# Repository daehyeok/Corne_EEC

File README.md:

# Corne EEC (Corne Extended Electrostatic Capacitive)

A Corne-based electrostatic capacitive (EC) keyboard featuring a number row and one additional thumb key.

> [!WARNING]
> I am not an electrical engineer. PCB design may not be optimized and could contain bugs. Use this project at your own risk.

## Features
* Corne-like design with a number row and 4 thumb keys, totaling 28 keys per half.
* Onboard STM32G431KBT6 MCU and USB-C with ESD protection.
* No through-hole components.
* ~~Extra PCB connectivity via a 1x06 FFC connector~~ **Rev2's FFC connector located upside down.**

## Firmware

The Rust-based firmware is hosted in a separate repository: [daehyeok/corne-eec-rs](https://github.com/daehyeok/corne-eec-rs).

## Credit

# Credit & Reference.

* [tomsmalley/custom-topre-guide](https://github.com/tomsmalley/custom-topre-guide): An invaluable resource for understanding custom Topre-style keyboards.
* [Cipulot](https://github.com/Cipulot)'s multiple PCB and firmware projects: A great source of inspiration for keyboard hardware and firmware development.
*  This project is forked from [Cipulot/CorneECRevival](https://github.com/Cipulot/CorneECRevival).

## Copyright

This project is released under the MIT License. Refer to the `LICENCE.md` file for details.

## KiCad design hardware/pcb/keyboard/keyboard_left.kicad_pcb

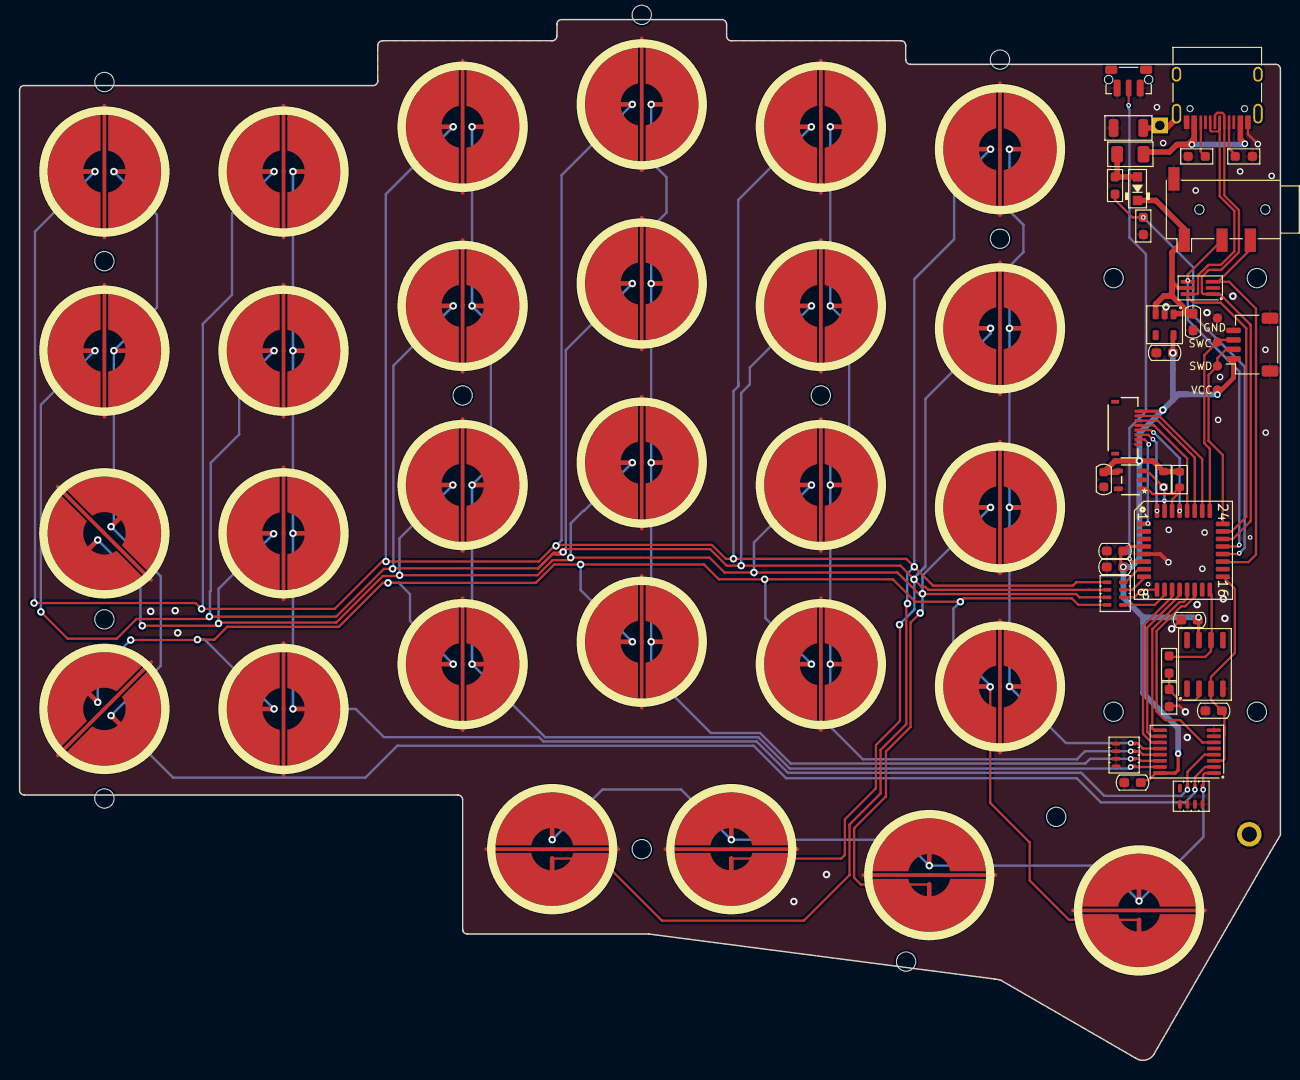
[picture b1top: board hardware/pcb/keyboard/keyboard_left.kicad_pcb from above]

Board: 2 copper layers, 133.8 x 110.4 mm, 108 parts (1 on the bottom side), 46 nets.

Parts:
C2, C3, C4: 0.1uF; C_0603_1608Metric_Pad1.05x0.95mm
C5: 4.7u; C_0603_1608Metric_Pad1.05x0.95mm
C8, C9: 1uF; C_0603_1608Metric_Pad1.05x0.95mm
C10: 220pF; C_0603_1608Metric_Pad1.05x0.95mm
C14: 10n; C_0603_1608Metric
D1: 1N5819; D_SOD-323_HandSoldering
F1: 500mA; Fuse_1206_3216Metric
G1, G2, G3, G4, G5, G6, G7, G8, G9, G10, G11, G12, G13, G14, G15, G16, G17, G18, G19, G20, G21, G23, G24, G25, G26, G27, G28: ecs_housing_graphic
G22: ecs_housing_graphic_1.5U
H0: SMT-SO-M1.6-with-ring
H1, H2, H3, H4, H5, H6, H7, H8, H9, H10, H11, H12, H13, H14, H15, H16: MountingHole_2.05mm
H17: PinHeader_1x01
J1: SM04B-SRSS-TB; JST_SH_SM04B-SRSS-TB_1x04-1MP_P1.00mm_Horizontal
J2: PJ320D; Jack_3.5mm_PJ320D_Horizontal
J3: HRO_TYPE-C-31-M-12; USB_C_Receptacle_HRO_TYPE-C-31-M-12
J4: Conn_01x08_MountingPin; CONN8_FH34SRJ_HIR
L1: 60R@100MHz; L_1206_3216Metric
R2, R3: 5.1k; R_0603_1608Metric_Pad0.98x0.95mm
R4: < 800; R_0603_1608Metric_Pad0.98x0.95mm
R5, R6: 1k; R_0603_1608Metric_Pad0.98x0.95mm
R7: 100k; R_0603_1608Metric_Pad0.98x0.95mm
R9, R10: 10k; R_0603_1608Metric
RN1, RN2: 1k R_Array_Concave_4x0603; R_Array_Concave_4x0603
RN3: 100 R_Array_Convex_4x1206; R_Array_Concave_4x0603
SW1, SW2, SW3, SW4, SW5, SW6, SW7, SW8, SW9, SW10, SW11, SW12, SW13, SW14, SW15, SW16, SW17, SW18, SW19, SW20, SW21, SW22, SW23, SW24, SW25, SW26, SW27, SW28: ecs_pad_no_ring
SW29: PTS845; SW_Push_1P1T-MP_NO_Horizontal_Alps_SKRTLAE010
TP1: PinHeader_1x04_P2.54mm_test_pad
U1: 74HC4051; TSSOP-16_4.4x5mm_P0.65mm
U2: OPA350UA; SO-8_3.9x4.9mm_P1.27mm
U3: DT1446-04S; SOT-363_SC-70-6_Handsoldering
U4: XC6220B331MR-G; SOT-23-5
U5: STM32G0B1KETx; LQFP-32_7x7mm_P0.8mm
U6: 24FC01T-I/OT; SOT-23-5_2P9X1P6_MCH

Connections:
+3V3: C2.2, C3.2, C4.1, C5.1, C8.1, C14.2, J1.1, J4.1, R9.2, R10.1, TP1.1, U1.16 (VCC), U2.7 (V+), U4.5 (VOUT), U5.4 (VDD), U6.4 (VCC)
+5V: C9.1, D1.1 (K), J2.T, U3.5 (VP), U4.1 (VIN), U4.3 (EN)
/NRST: SW29.2, U5.6 (PF2)
/PA15: J4.2, U5.26 (PA15)
/PB3: J4.3, U5.27 (PB3)
/PB4: J4.4, U5.28 (PB4)
/PB5: J4.5, U5.29 (PB5)
/PB8: J4.6, U5.32 (PB8)
/PB9: J4.7, U5.1 (PB9)
A1: RN1.2 (R2.1), SW11.1, SW12.1, SW13.1, SW25.1, U1.14 (A1)
A2: RN1.1 (R1.1), SW8.1, SW9.1, SW10.1, SW24.1, U1.15 (A2)
A3: RN1.4 (R4.1), SW17.1, SW18.1, SW19.1, SW27.1, U1.12 (A3)
A4: RN2.1 (R1.1), SW20.1, SW21.1, SW22.1, SW28.1, U1.1 (A4)
A6: RN2.2 (R2.1), SW1.1, SW2.1, SW3.1, SW4.1, U1.2 (A6)
A7: RN2.3 (R3.1), SW5.1, SW6.1, SW7.1, SW23.1, U1.4 (A7)
ADC: R7.1, U2.6, U5.16 (PB1)
AO: RN1.3 (R3.1), SW14.1, SW15.1, SW16.1, SW26.1, U1.13 (A0)
CHARGE_RST: C10.1, U1.3 (A), U2.3 (+), U5.17 (PB2)
CSEL0: U1.11 (S0), U5.11 (PA4)
CSEL1: U1.10 (S1), U5.12 (PA5)
CSEL2: U1.9 (S2), U5.13 (PA6)
CSEL_EN: U1.6 (~E), U5.14 (PA7)
D+: J3.A6 (D+), J3.B6 (D+), U3.6 (IO4), U5.23 (PA12/PA10)
D-: J3.A7 (D-), J3.B7 (D-), U3.1 (IO1), U5.22 (PA11/PA9)
GND: C2.1, C3.1, C4.2, C5.2, C8.2, C9.2, C10.2, C14.1, H0.1, J1.4, J1.MP (MountPin), J2.S, J3.A1 (GND), J3.A12 (GND), J3.B1 (GND), J3.B12 (GND), J4.8, L1.1, R2.2, R3.2, R5.2, R6.2, RN1.5 (R4.2), RN1.6 (R3.2), RN1.7 (R2.2), RN1.8 (R1.2), RN2.5 (R4.2), RN2.6 (R3.2), RN2.7 (R2.2), RN2.8 (R1.2), SW1.3 (SG), SW2.3 (SG), SW3.3 (SG), SW4.3 (SG), SW5.3 (SG), SW6.3 (SG), SW7.3 (SG), SW8.3 (SG), SW9.3 (SG), SW10.3 (SG), SW11.3 (SG), SW12.3 (SG), SW13.3 (SG), SW14.3 (SG), SW15.3 (SG), SW16.3 (SG), SW17.3 (SG), SW18.3 (SG), SW19.3 (SG), SW20.3 (SG), SW21.3 (SG), SW22.3 (SG), SW23.3 (SG), SW24.3 (SG), SW25.3 (SG), SW26.3 (SG), SW27.3 (SG), SW28.3 (SG), SW29.1, TP1.4, U1.7 (VEE), U1.8 (GND), U2.4 (V-), U3.2 (VN), U4.2 (GND), U5.5 (VSS), U6.2 (VSS), U6.5 (WP)
GNDPWR: H17.1, J3.S2 (SHIELD), L1.2
I2C1_SCL: R10.2, U5.30 (PB6), U6.1 (SCL)
I2C1_SDA: R9.1, U5.31 (PB7), U6.3 (SDA)
unnamed: D1.2 (A), F1.1, R4.1
unnamed: J3.A5 (CC1), R2.1
unnamed: J3.B5 (CC2), R3.1
unnamed: R6.1, R7.2, U2.2 (-)
ROW0: RN3.5 (R4.2), SW1.2, SW23.2, SW24.2, SW25.2, SW26.2, SW27.2, SW28.2
ROW1: RN3.6 (R3.2), SW2.2, SW5.2, SW8.2, SW11.2, SW14.2, SW17.2, SW20.2
ROW2: RN3.7 (R2.2), SW3.2, SW6.2, SW9.2, SW12.2, SW15.2, SW18.2, SW21.2
ROW3: RN3.8 (R1.2), SW4.2, SW7.2, SW10.2, SW13.2, SW16.2, SW19.2, SW22.2
SWCLK: J1.3, TP1.3, U5.25 (PA14)
SWDIO: J1.2, TP1.2, U5.24 (PA13)
TX0: RN3.4 (R4.1), U5.7 (PA0)
TX1: RN3.3 (R3.1), U5.8 (PA1)
TX2: RN3.2 (R2.1), U5.9 (PA2)
TX3: RN3.1 (R1.1), U5.10 (PA3)
USART_RX: J2.R1, U3.4 (IO3), U5.21 (PA10/UCPD1_DBCC2)
USART_TX: J2.R2, U3.3 (IO2), U5.19 (PA9/UCPD1_DBCC1)
VBUS: F1.2, J3.A4 (VBUS), J3.A9 (VBUS), J3.B4 (VBUS), J3.B9 (VBUS)
VBUS_DEC: R4.2, R5.1, U5.20 (PC6)

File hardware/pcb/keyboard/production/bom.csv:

Designator,Footprint,Quantity,Value,LCSC Part #
C10,0603,1,220pF,C5255295
C14,0603,1,10n,C307331
"C2, C3",0603,2,0.1uF,C19702
C4,0603,1,0.1uF,C307331
C5,0603,1,4.7u,C307331
"C8, C9",0603,2,1uF,
D1,D_SOD-323_HandSoldering,1,1N5819,
F1,1206,1,500mA,C70076
"G1, G10, G11, G12, G13, G14, G15, G16, G17, G18, G19, G2, G20, G21, G23, G24, G25, G26, G27, G28, G3, G4, G5, G6, G7, G8, G9",ecs_housing_graphic,27,~,
G22,ecs_housing_graphic_1.5U,1,~,
H0,SMT-SO-M1.6-with-ring,1,~,
"H1, H10, H11, H12, H13, H14, H15, H16, H2, H3, H4, H5, H6, H7, H8, H9",MountingHole_2.05mm,16,~,
H17,PinHeader_1x01,1,~,
J1,JST_SH_SM04B-SRSS-TB_1x04-1MP_P1.00mm_Horizontal,1,SM04B-SRSS-TB,
J2,Jack_3.5mm_PJ320D_Horizontal,1,PJ320D,
J3,USB_C_Receptacle_HRO_TYPE-C-31-M-12,1,HRO_TYPE-C-31-M-12,
J4,CONN8_FH34SRJ_HIR,1,Conn_01x08_MountingPin,
L1,1206,1,60R@100MHz,
R1,0603,1,1k,
"R10, R4, R9",0603,3,10k,
"R2, R3",0603,2,5.1k,
R5,0603,1,5.6k,
R6,0603,1,1k,C3152127
R7,0603,1,100k,C3152121
"RN1, RN2",R_Array_Concave_4x0603,2,1k R_Array_Concave_4x0603,
RN3,R_Array_Concave_4x0603,1,100 R_Array_Convex_4x0603,
"SW1, SW10, SW11, SW12, SW13, SW14, SW15, SW16, SW17, SW18, SW19, SW2, SW20, SW21, SW22, SW23, SW24, SW25, SW26, SW27, SW28, SW3, SW4, SW5, SW6, SW7, SW8, SW9",ecs_pad_no_ring,28,~,
SW29,SW_Push_1P1T-MP_NO_Horizontal_Alps_SKRTLAE010,1,PTS845,
TP1,PinHeader_1x04_P2.54mm_test_pad,1,~,
U1,TSSOP-16_4.4x5mm_P0.65mm,1,74HC4051,C5645
U2,SO-8_3.9x4.9mm_P1.27mm,1,OPA350UA,
U3,SOT-363_SC-70-6_Handsoldering,1,DT1446-04S,
U4,SOT-23-5,1,XC6220B331MR-G,
U5,LQFP-32_7x7mm_P0.8mm,1,STM32G0B1KETx,
U6,SOT-23-5_2P9X1P6_MCH,1,24FC01T-I/OT,

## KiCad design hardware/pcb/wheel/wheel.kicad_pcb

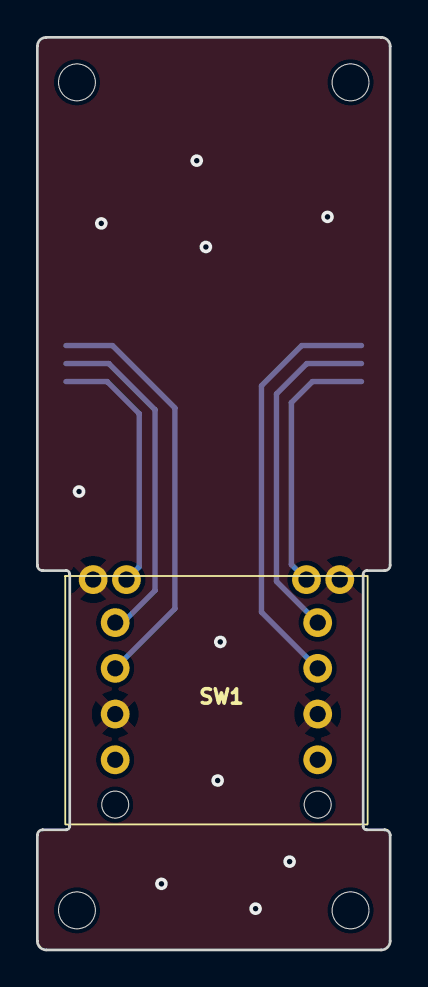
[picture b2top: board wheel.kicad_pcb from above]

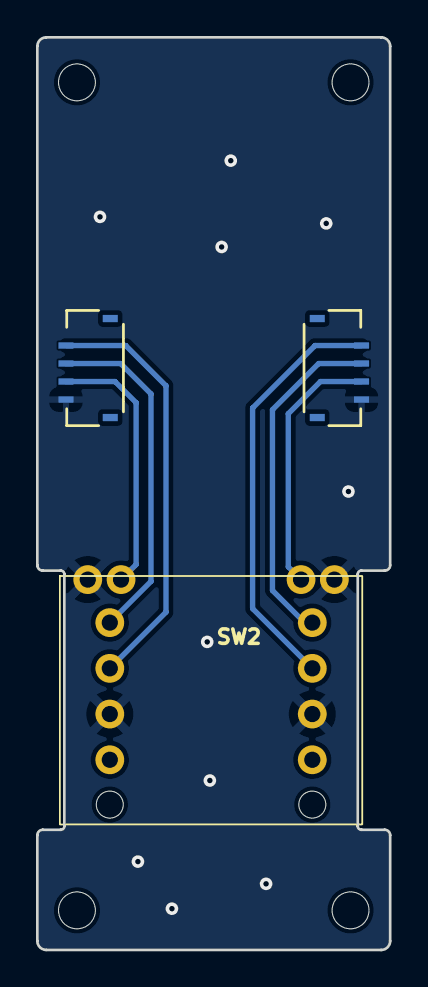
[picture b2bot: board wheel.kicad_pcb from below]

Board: 2 copper layers, 19.6 x 50.7 mm, 8 parts (3 on the bottom side), 7 nets.

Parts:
H3, H4, H5, H6: MountingHole_2.05mm
J1, J4: Conn_01x08_MountingPin; CONN8_FH34SRJ_HIR
SW1, SW2: RotaryEncoder_Switch; EVQWGD001

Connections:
ACCS_1: J4.2, SW1.B
ACCS_1_2: J1.7, SW2.B
ACCS_2: J4.4, SW1.A
ACCS_2_2: J1.5, SW2.A
ACCS_3: J4.6, SW1.S2
ACCS_3_2: J1.3, SW2.S2
GND: J1.1, J4.8, SW1.C, SW1.S1, SW2.C, SW2.S1

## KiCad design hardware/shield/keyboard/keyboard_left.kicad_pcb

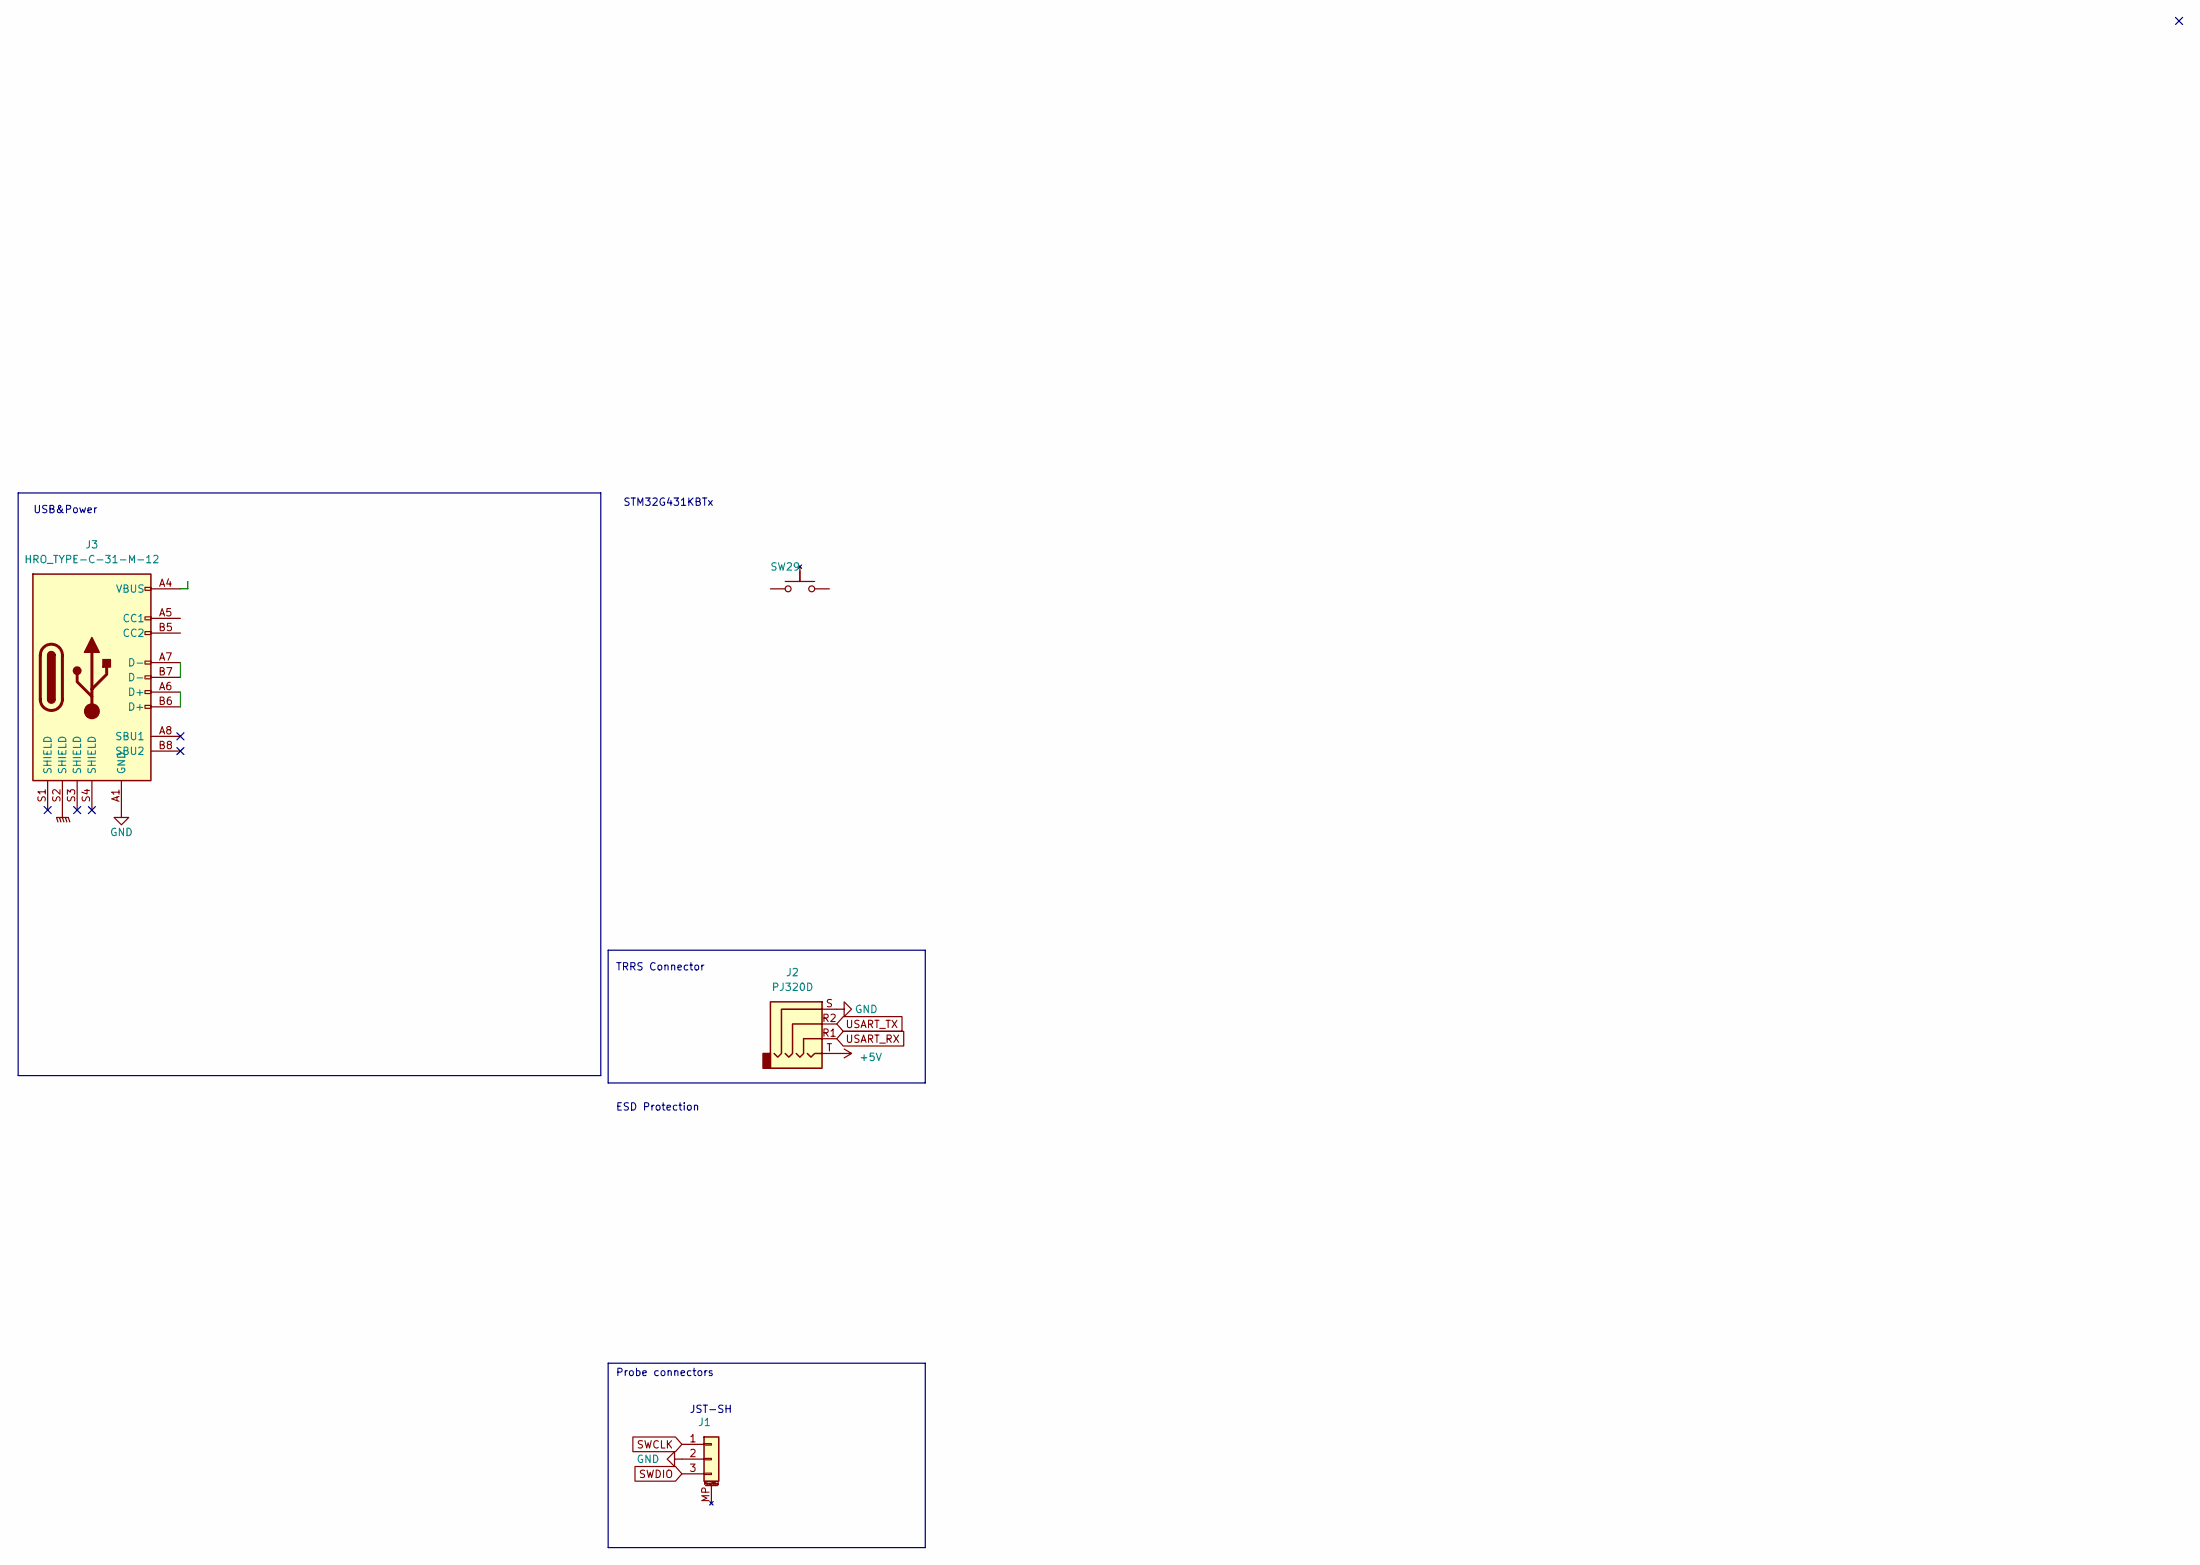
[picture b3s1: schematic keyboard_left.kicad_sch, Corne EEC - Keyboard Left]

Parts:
J1: SM03B-SRSS-TB; JST_SH_SM03B-SRSS-TB_1x03-1MP_P1.00mm_Horizontal
J2: PJ320D; Jack_3.5mm_PJ320D_Horizontal
J3: HRO_TYPE-C-31-M-12; USB_C_Receptacle_HRO_TYPE-C-31-M-12
SW29: PTS845; SW_Push_1P1T-MP_NO_Horizontal_Alps_SKRTLAE010

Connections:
+5V: J2.T
GND: J1.2, J2.S, J3.A1 (GND), J3.A12 (GND), J3.B1 (GND), J3.B12 (GND)
GNDPWR: J3.S2 (SHIELD)
unnamed: J3.A6 (D+), J3.B6 (D+)
unnamed: J3.A7 (D-), J3.B7 (D-)
unnamed: J3.A4 (VBUS), J3.A9 (VBUS), J3.B4 (VBUS), J3.B9 (VBUS)
SWCLK: J1.1
SWDIO: J1.3
USART_RX: J2.R1
USART_TX: J2.R2

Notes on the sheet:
Probe connectors
TRRS Connector
USB&Power
JST-SH
ESD Protection
STM32G431KBTx

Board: 2 copper layers, 4 parts (0 on the bottom side), 4 nets, no tracks yet.

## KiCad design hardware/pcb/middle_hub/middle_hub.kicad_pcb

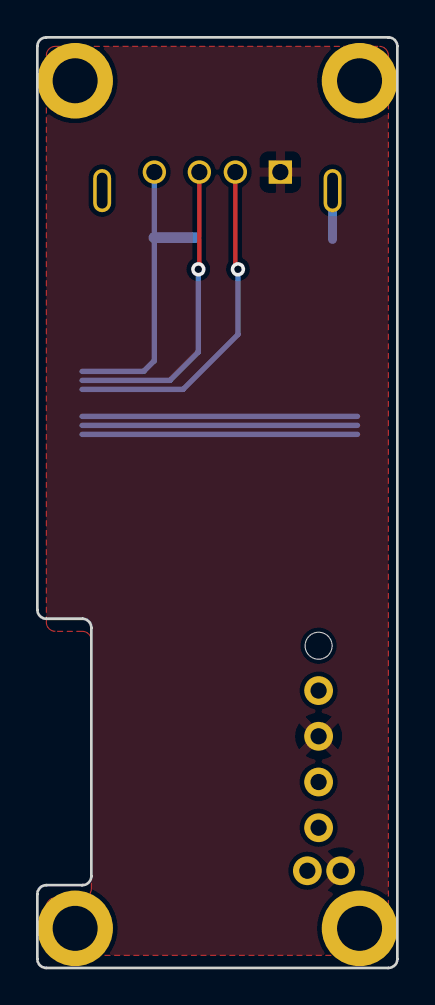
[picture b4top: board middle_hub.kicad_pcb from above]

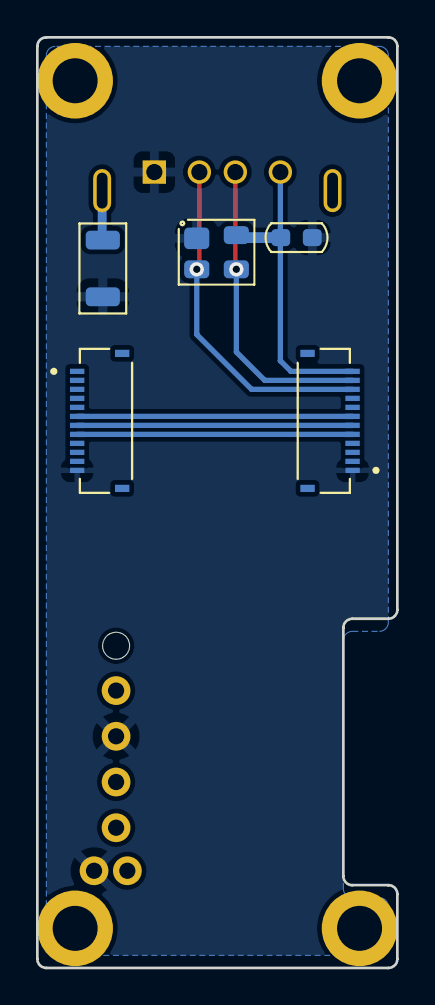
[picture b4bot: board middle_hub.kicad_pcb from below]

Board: 2 copper layers, 20.0 x 51.7 mm, 11 parts (5 on the bottom side), 8 nets.

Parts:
C1: C_Small; C_0603_1608Metric_Pad1.05x0.95mm
H13, H14, H15, H16: SMT-SO-M1.6-with-ring
J1: USB_A; USB_A_Molex_105057_Vertical
J2, J3: FH34SRJ-12S-0.5SH; HRS_FH34SRJ-12S-0.5SH(50)
L1: 60R@100MHz; L_1206_3216Metric
SW1: RotaryEncoder_Switch; EVQWGD001
U5: PRTR5V0U2X; SOT-143

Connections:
/DM4: J1.2 (D-), J2.11, U5.3 (I/O2)
/DP4: J1.3 (D+), J2.10, U5.2 (I/O1)
ENC_S1: J2.5, J3.8, SW1.S2
GND: C1.1, J1.4 (GND), J2.1, J3.12, L1.1, SW1.C, SW1.S1, U5.1 (GND)
INPUT_A: J2.7, J3.6
INPUT_B: J2.6, J3.7
unnamed: J1.5 (Shield), L1.2
VBUS: C1.2, J1.1 (VBUS), J2.12, U5.4 (VCC)

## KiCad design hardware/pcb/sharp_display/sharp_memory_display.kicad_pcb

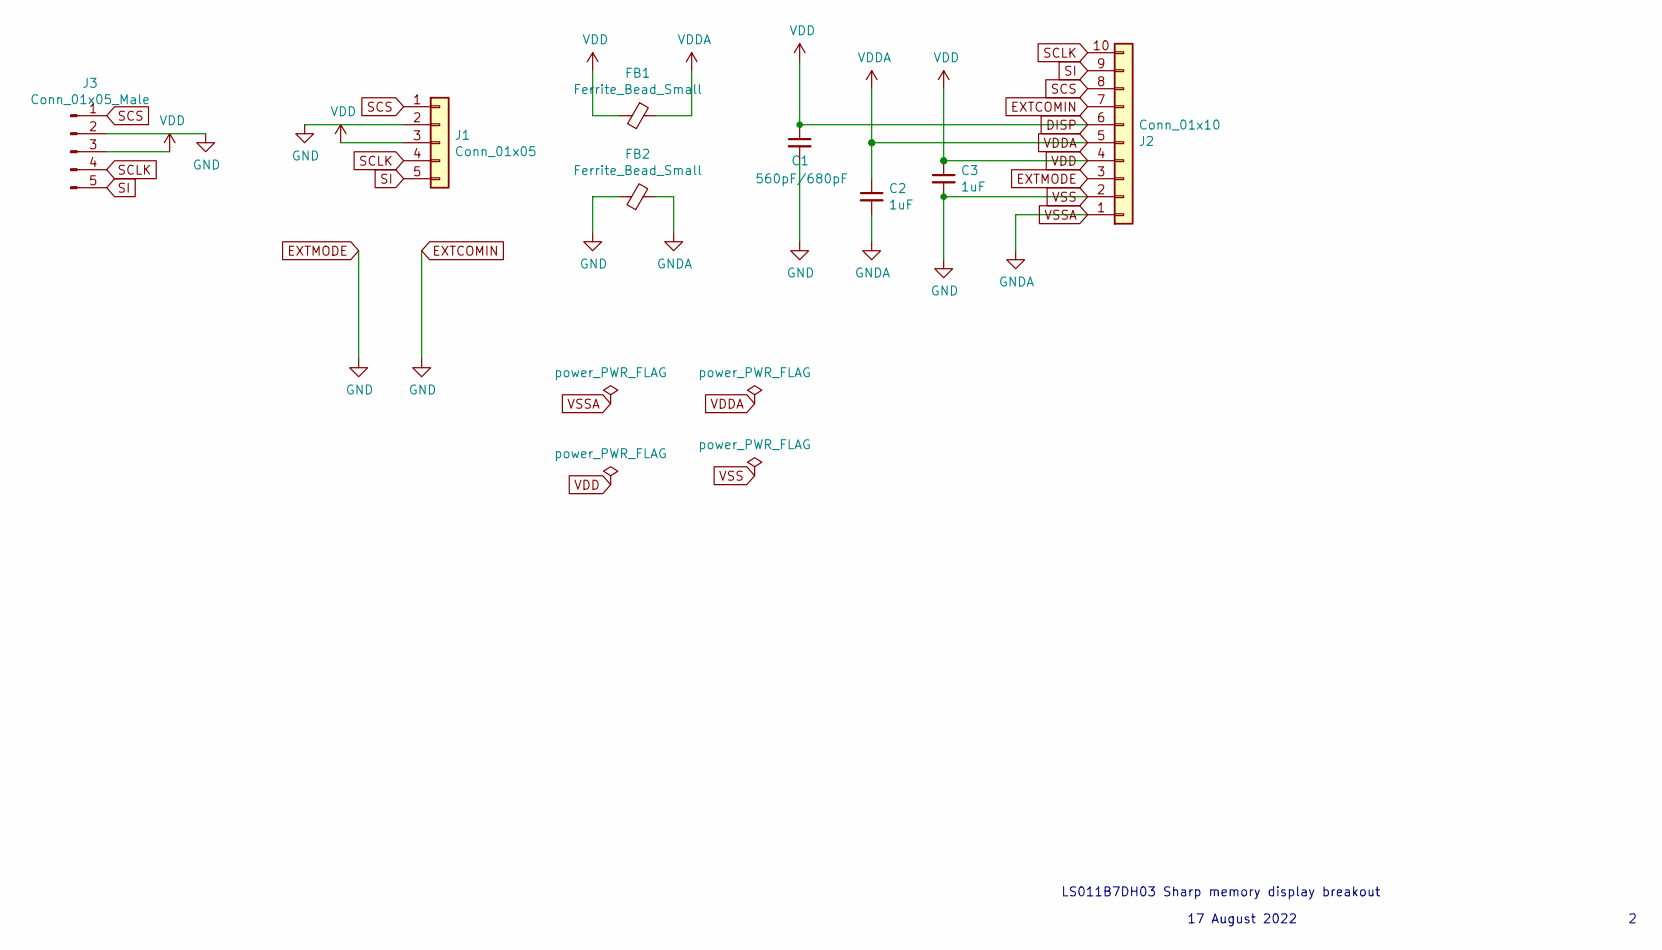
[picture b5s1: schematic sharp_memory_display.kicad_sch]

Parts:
C1: 560pF/680pF; C_0603_1608Metric_Pad1.08x0.95mm; LCSC C84721
C2, C3: 1uF; C_0603_1608Metric_Pad1.08x0.95mm; LCSC C15849
FB1, FB2: Ferrite_Bead_Small; L_0603_1608Metric_Pad1.05x0.95mm; LCSC C1017
J1: Conn_01x05; PinSocket_1x05_P2.54mm_Vertical
J2: Conn_01x10; HRS_FH34SRJ-10S-0.5SH(50); LCSC C506791
J3: Conn_01x05_Male; JST_SH_SM05B-SRSS-TB_1x05-1MP_P1.00mm_Horizontal

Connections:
DISP: C1.1, C3.1, FB1.2, J1.3, J2.4, J2.6, J3.3
EXTCOMIN: C1.2, C3.2, FB2.1, J1.2, J2.2, J2.3, J2.7, J3.2
SCLK: J1.4, J2.10, J3.4
SCS: J1.1, J2.8, J3.1
SI: J1.5, J2.9, J3.5
VDDA: C2.1, FB1.1, J2.5
VSSA: C2.2, FB2.2, J2.1

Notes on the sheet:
17 August 2022
LS011B7DH03 Sharp memory display breakout

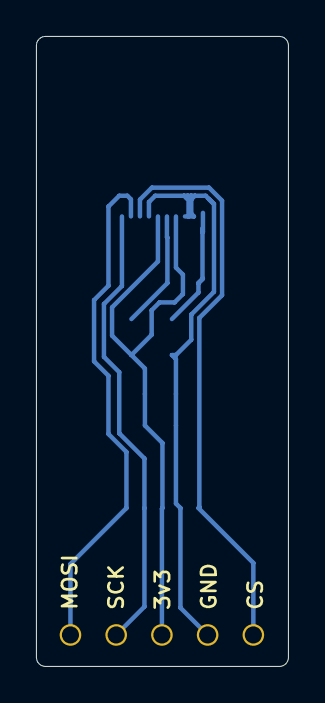
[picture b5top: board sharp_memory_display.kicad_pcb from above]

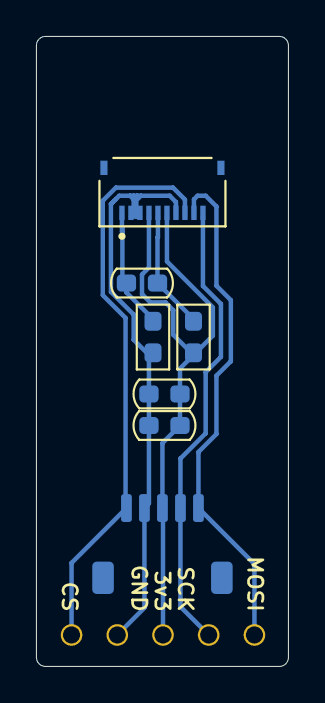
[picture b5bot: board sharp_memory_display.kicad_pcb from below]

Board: 2 copper layers, 14.0 x 35.0 mm, 8 parts (7 on the bottom side), 7 nets.

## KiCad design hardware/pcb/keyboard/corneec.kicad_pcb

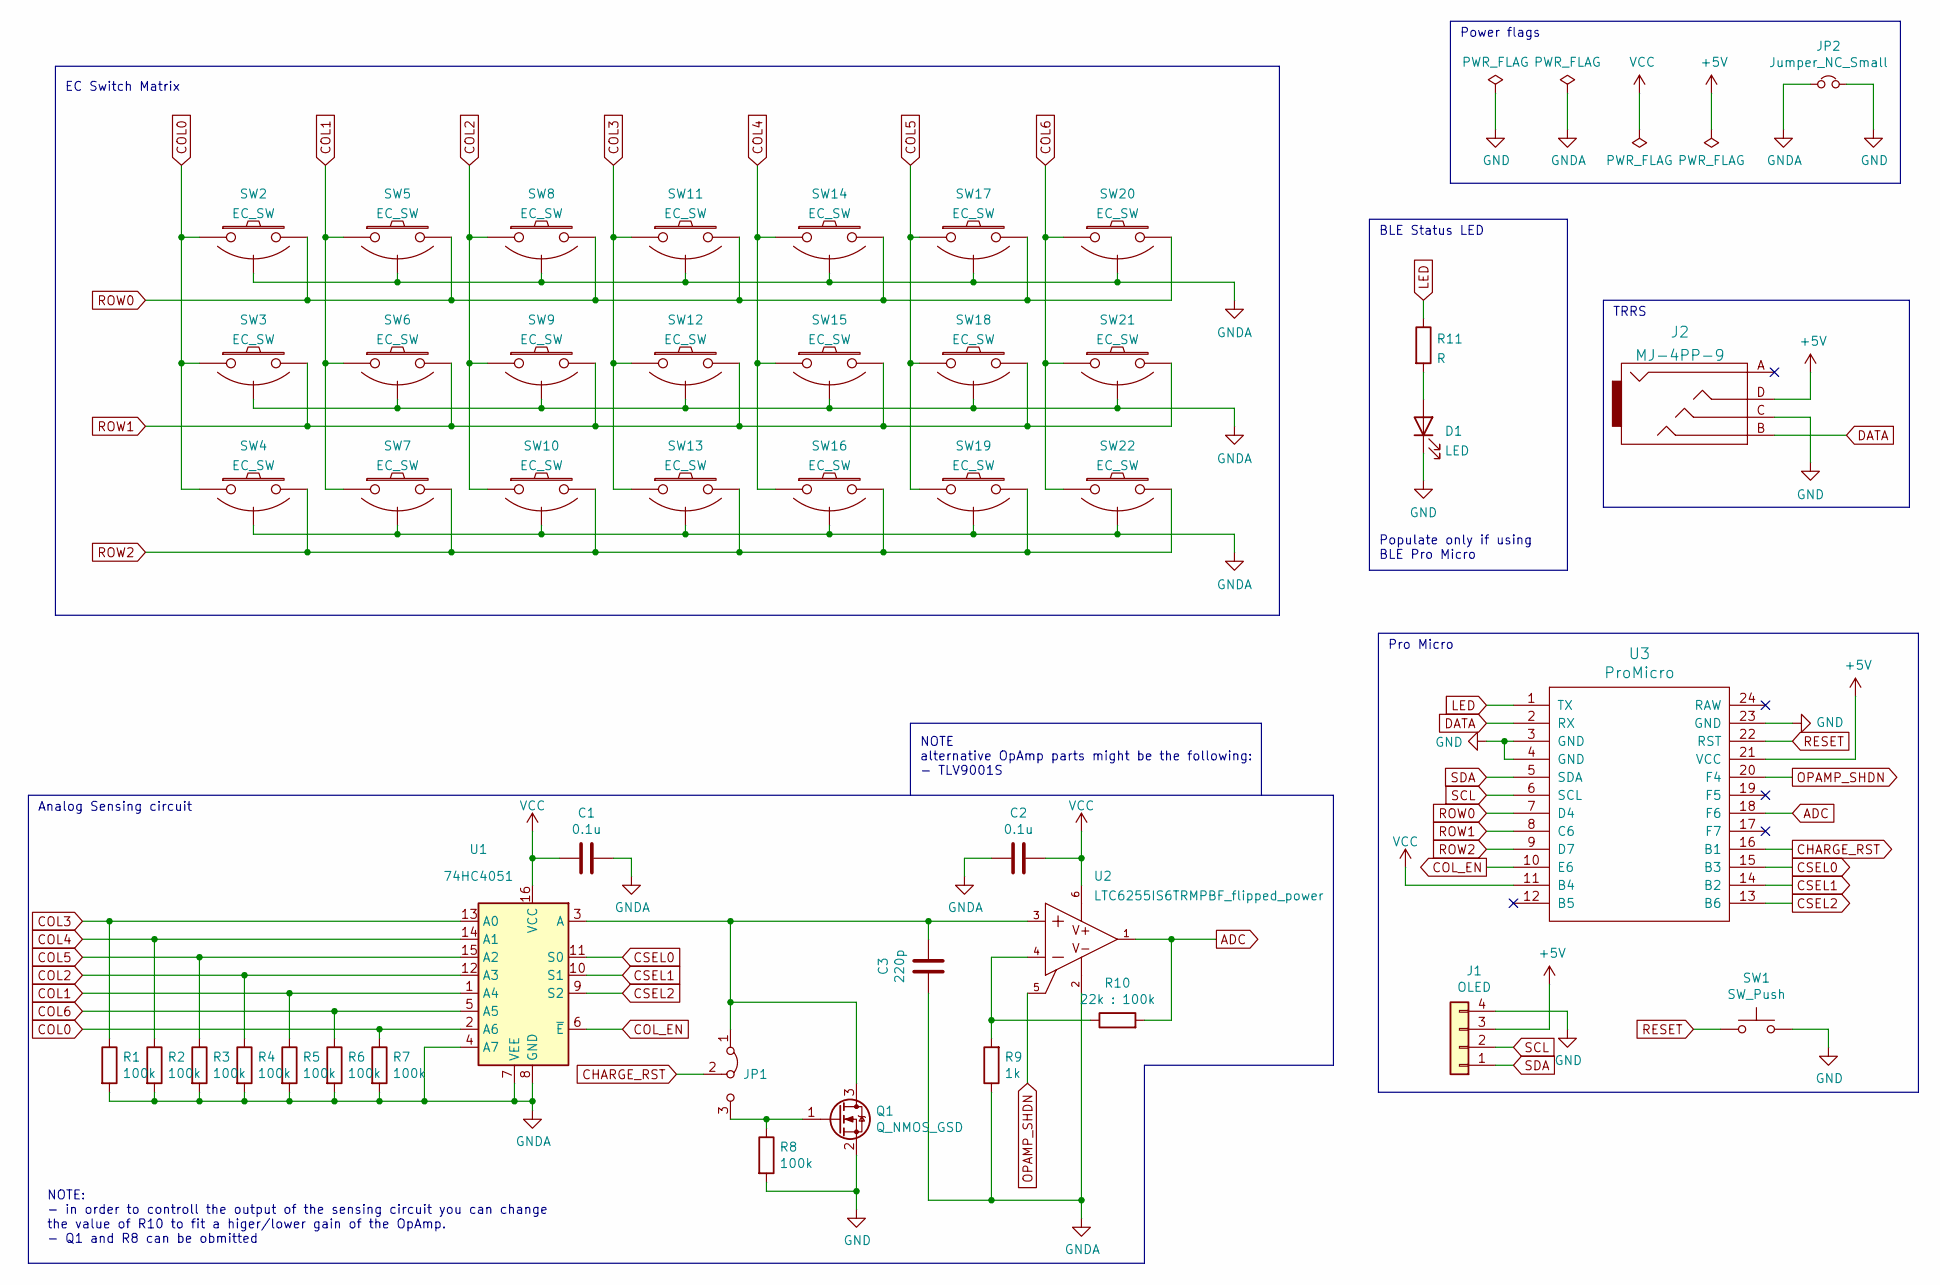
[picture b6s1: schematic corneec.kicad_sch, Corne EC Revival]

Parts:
C1, C2: 0.1u; C_0603_1608Metric_Pad1.08x0.95mm_HandSolder
C3: 220p; C_0603_1608Metric_Pad1.08x0.95mm_HandSolder
D1: LED; D_0603_1608Metric
J1: OLED; OLED_Small
J2: MJ-4PP-9; TRRS-PJ-320A-no-Fmask
JP1: Jumper_3_Bridged12; SolderJumper-3_P1.3mm_Bridged12_Pad1.0x1.5mm
JP2: Jumper_NC_Small; SolderJumper-2_P1.3mm_Bridged_Pad1.0x1.5mm
Q1: Q_NMOS_GSD; SOT-23
R1, R2, R3, R4, R5, R6, R7, R8: 100k; R_0603_1608Metric_Pad0.98x0.95mm_HandSolder
R9: 1k; R_0603_1608Metric_Pad0.98x0.95mm_HandSolder
R10: 22k : 100k; R_0603_1608Metric_Pad0.98x0.95mm_HandSolder
R11: R; R_0603
SW1: SW_Push; SW_3.5x6.0_TH
SW2, SW3, SW4, SW5, SW6, SW7, SW8, SW9, SW10, SW11, SW12, SW13, SW14, SW15, SW16, SW17, SW18, SW19, SW20, SW21, SW22: EC_SW; ecs_pad
U1: 74HC4051; TSSOP16
U2: LTC6255IS6TRMPBF_flipped_power; TSOT-23-6_HandSoldering
U3: ProMicro; Sparkfun_Pro_Micro

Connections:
+5V: J1.3, J2.D, U3.21 (VCC)
ADC: R10.2, U2.1 (OUT), U3.18 (F6)
CHARGE_RST: JP1.2 (C), U3.16 (B1)
COL0: R7.1, SW2.1, SW3.1, SW4.1, U1.2 (A6)
COL1: R5.1, SW5.1, SW6.1, SW7.1, U1.1 (A4)
COL2: R4.1, SW8.1, SW9.1, SW10.1, U1.12 (A3)
COL3: R1.1, SW11.1, SW12.1, SW13.1, U1.13 (A0)
COL4: R2.1, SW14.1, SW15.1, SW16.1, U1.14 (A1)
COL5: R3.1, SW17.1, SW18.1, SW19.1, U1.15 (A2)
COL6: R6.1, SW20.1, SW21.1, SW22.1, U1.5 (A5)
COL_EN: U1.6 (~E), U3.10 (E6)
CSEL0: U1.11 (S0), U3.15 (B3)
CSEL1: U1.10 (S1), U3.14 (B2)
CSEL2: U1.9 (S2), U3.13 (B6)
DATA: J2.B, U3.2 (RX)
GND: D1.1 (K), J1.4, J2.C, JP2.2, Q1.2 (S), R8.2, SW1.2, U3.3 (GND), U3.4 (GND), U3.23 (GND)
GNDA: C1.1, C2.2, C3.2, JP2.1, R1.2, R2.2, R3.2, R4.2, R5.2, R6.2, R7.2, R9.1, SW2.3 (SG), SW3.3 (SG), SW4.3 (SG), SW5.3 (SG), SW6.3 (SG), SW7.3 (SG), SW8.3 (SG), SW9.3 (SG), SW10.3 (SG), SW11.3 (SG), SW12.3 (SG), SW13.3 (SG), SW14.3 (SG), SW15.3 (SG), SW16.3 (SG), SW17.3 (SG), SW18.3 (SG), SW19.3 (SG), SW20.3 (SG), SW21.3 (SG), SW22.3 (SG), U1.4 (A7), U1.7 (VEE), U1.8 (GND), U2.2 (V-)
LED: R11.1, U3.1 (TX)
unnamed: C3.1, JP1.1 (A), Q1.3 (D), U1.3 (A), U2.3 (+IN)
unnamed: D1.2 (A), R11.2
unnamed: JP1.3 (B), Q1.1 (G), R8.1
unnamed: R9.2, R10.1, U2.4 (-IN)
OPAMP_SHDN: U2.5 (~SHDN), U3.20 (F4)
RESET: SW1.1, U3.22 (RST)
ROW0: SW2.2, SW5.2, SW8.2, SW11.2, SW14.2, SW17.2, SW20.2, U3.7 (D4)
ROW1: SW3.2, SW6.2, SW9.2, SW12.2, SW15.2, SW18.2, SW21.2, U3.8 (C6)
ROW2: SW4.2, SW7.2, SW10.2, SW13.2, SW16.2, SW19.2, SW22.2, U3.9 (D7)
SCL: J1.2, U3.6 (SCL)
SDA: J1.1, U3.5 (SDA)
VCC: C1.2, C2.1, U1.16 (VCC), U2.6 (V+), U3.11 (B4)

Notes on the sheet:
TRRS
NOTE alternative OpAmp parts might be the following: - TLV9001S
Populate only if using BLE Pro Micro
Pro Micro
NOTE: - in order to controll the output of the sensing circuit you can change the value of R10 to fit a higer/lower gain of the OpAmp. - Q1 and R8 can be obmitted
EC Switch Matrix
Analog Sensing circuit
BLE Status LED
Power flags

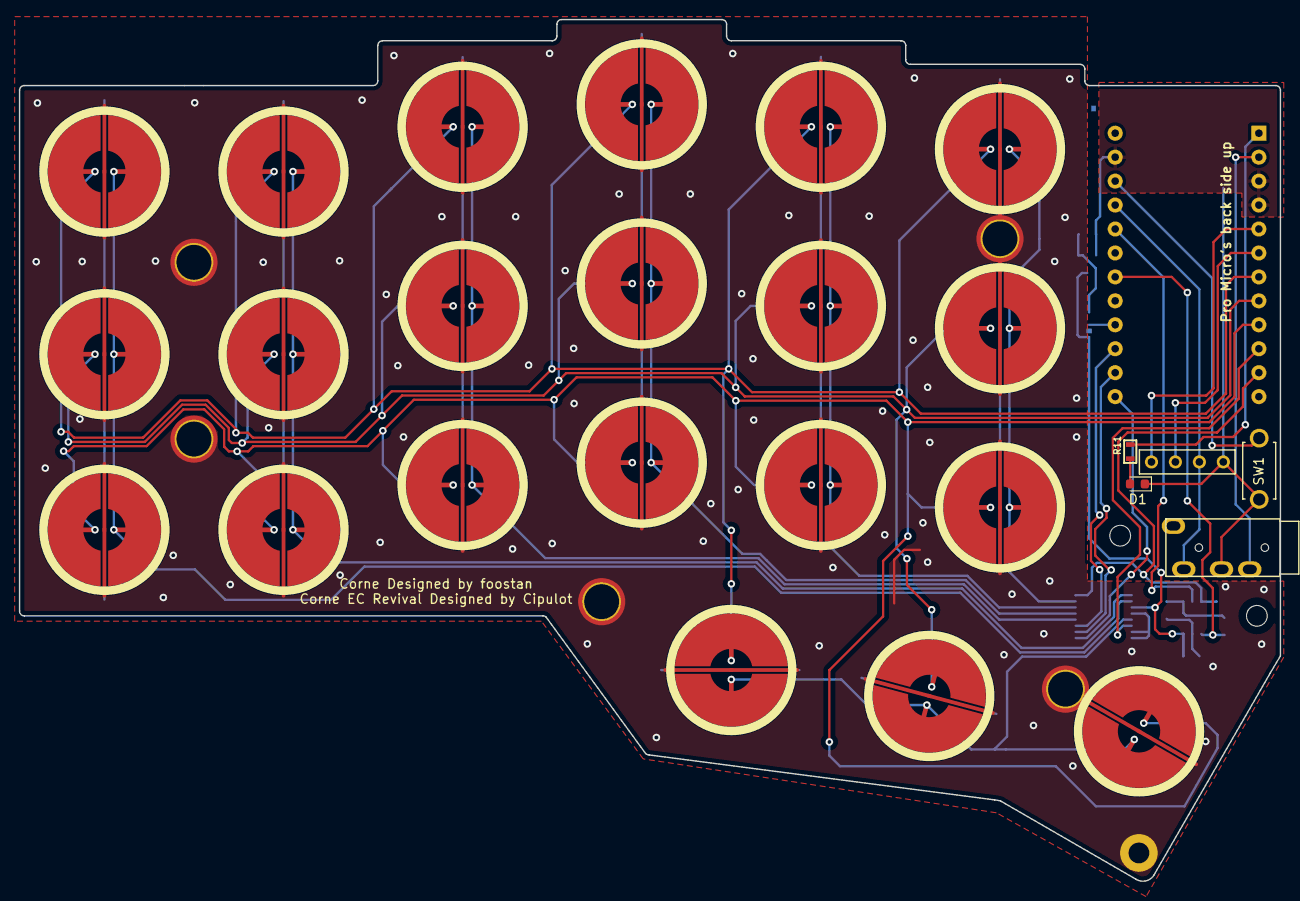
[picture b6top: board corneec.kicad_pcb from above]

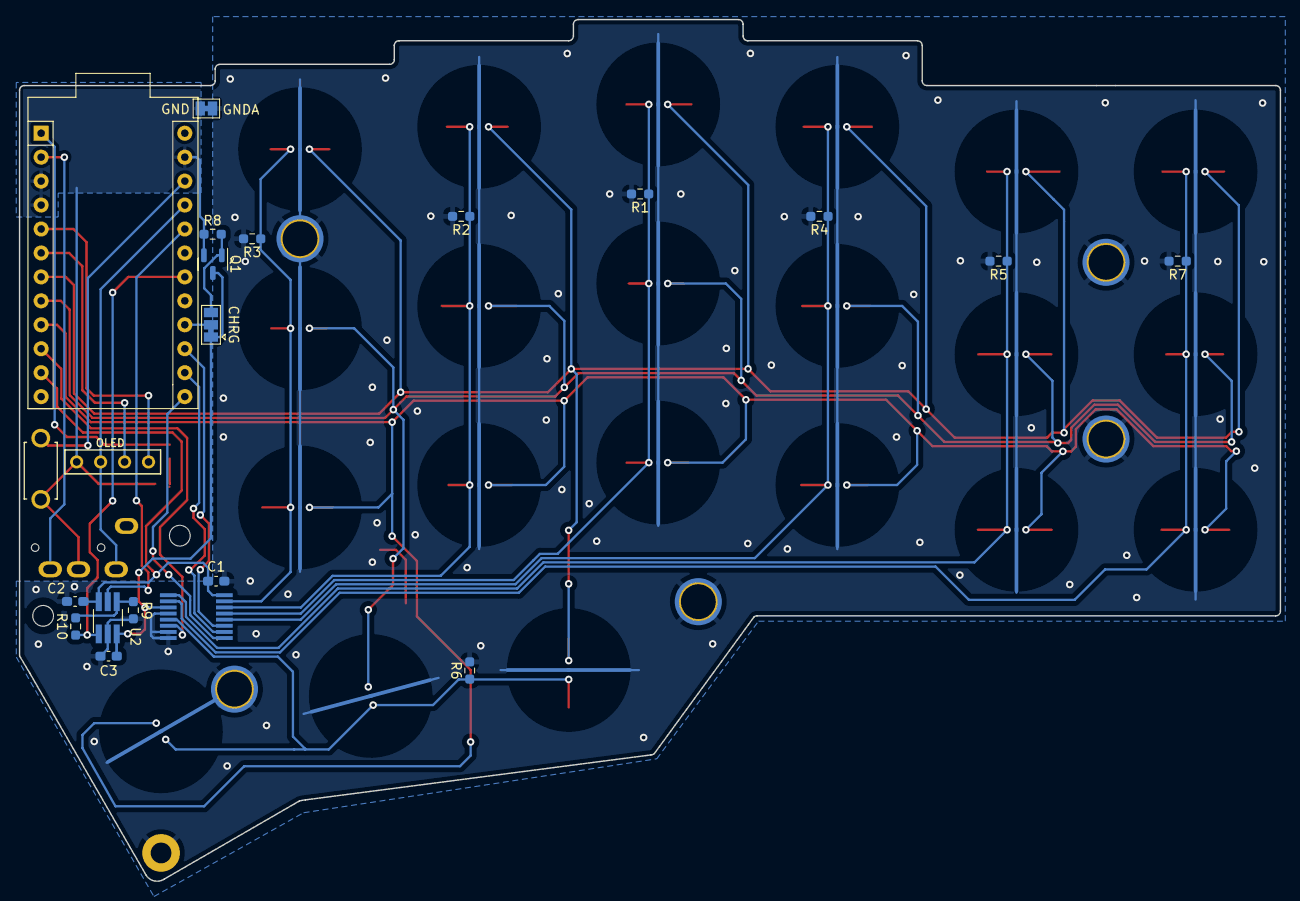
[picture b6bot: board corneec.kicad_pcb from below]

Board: 2 copper layers, 133.8 x 91.4 mm, 46 parts (19 on the bottom side), 30 nets.

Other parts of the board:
H22: MountingHole; HOLE_M2

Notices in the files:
PCB/corneec/corneec.kicad_sch:
Copyright © 2021 Cipulot
hardware/pcb/keyboard/keyboard_left.kicad_pcb:
Copyright © 2025
hardware/pcb/middle_hub/middle_hub.kicad_pcb:
Copyright © 2023
